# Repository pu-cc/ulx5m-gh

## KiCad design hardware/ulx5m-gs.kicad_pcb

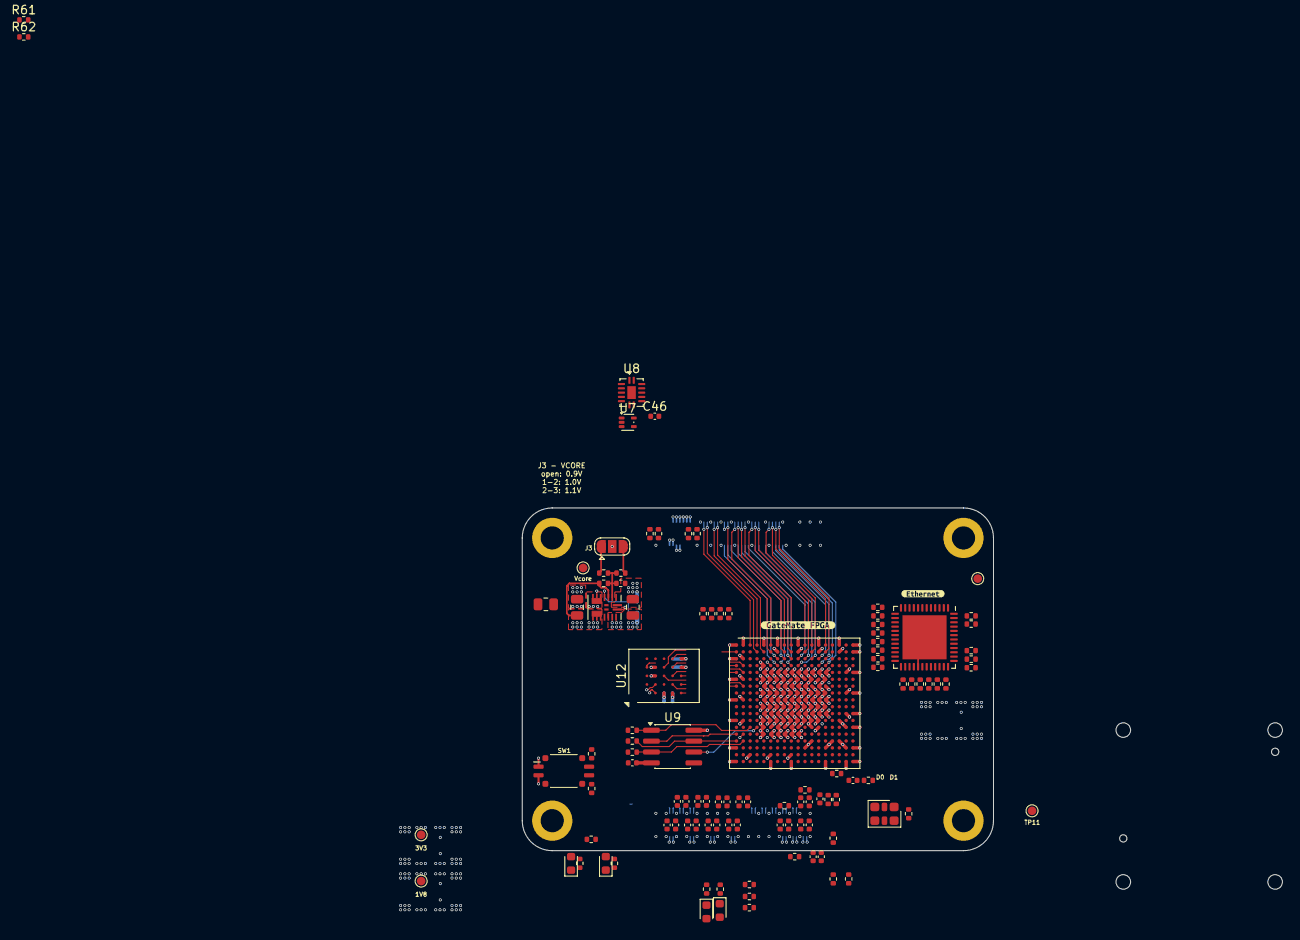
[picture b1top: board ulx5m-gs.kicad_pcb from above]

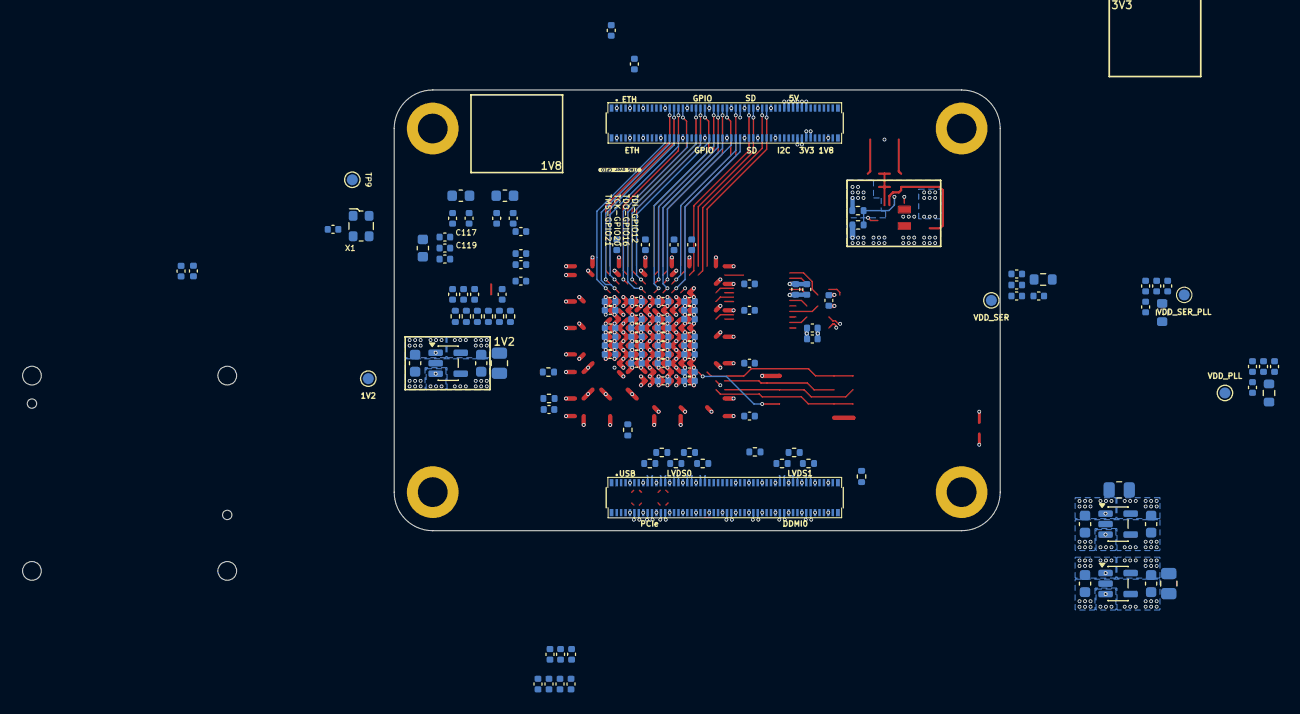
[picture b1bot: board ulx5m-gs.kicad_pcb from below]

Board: 4 copper layers, 88.7 x 44.5 mm, 243 parts (130 on the bottom side), 217 nets.

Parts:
C1, C10: 22u; C_0805_2012Metric
C2, C3, C8, C9, C11, C29: 1u; C_0603_1608Metric
C5, C6, C7, C12, C19, C20, C24, C25, C33, C59, C60, C61, C62, C63, C64, C65, C66, C87, C91, C95, C120, C121: 220n; C_0402_1005Metric
C13, C16, C21, C26, C36, C44, C51, C54, C75, C78, C86, C90, C94, C100, C122, C123, C131: 2u2; C_0402_1005Metric
C15, C18, C23, C28, C81, C82, C110, C111, C113, C119, C126, C139: 10n; C_0402_1005Metric
C31, C34, C37, C40, C42, C45, C46, C47, C48, C49, C52, C55, C56, C57, C76, C79, C80, C83, C84, C88, C89, C92, C93, C96, C97, C102, C103, C106, C107, C108, C112, C116, C117, C118, C127, C128, C129, C130, C132, C133, C134, C135, C136, C137, C138: 100n; C_0402_1005Metric
C39, C43, C50, C53, C58, C77, C98, C124, C125: 22u; C_0402_1005Metric
C104, C105, C109, C114: 10u; C_0402_1005Metric
C115: 4u7; C_0402_1005Metric
D1: green; D_0603_1608Metric
D2: red; D_0603_1608Metric
D9, D10: LED; LED_0603_1608Metric
FB1, FB2, FB3: BLM18PG121SN1D; L_0603_1608Metric
H1, H2, H3, H4: MountingHole; MountingHole_2.7mm_M2.5_DIN965_Pad
J1, J2: DF40C-100DP-0.4V_51_; HRS_DF40C-100DP-0.4V_51_
J3: Vcore_sel; SolderJumper-3_P1.3mm_Open_RoundedPad1.0x1.5mm
R1, R143: 100k; R_0402_1005Metric
R2: 51k; R_0402_1005Metric
R7, R8: 0R; R_0402_1005Metric
R9, R107, R108, R110, R112, R113: dnp; R_0402_1005Metric
R10, R11, R13, R21: 0R; R_0805_2012Metric
R12: 40k; R_0402_1005Metric
R14: 120k; R_0402_1005Metric
R15: 20k; R_0402_1005Metric
R16: 60k; R_0402_1005Metric
R23, R105, R106: 1R; R_0603_1608Metric
R24, R25, R27, R29, R30, R111, R128, R134, R138, R139, R147, R148, R149, R150: 10k; R_0402_1005Metric
R31, R32: 200R; R_0402_1005Metric
R33, R34, R35, R36, R38, R39, R66, R67, R70, R71, R72, R73, R78, R79, R84, R85, R96: 4k7; R_0402_1005Metric
R44, R45: 27; R_0402_1005Metric
R50, R51, R54, R129, R130, R131, R132, R135: 150; R_0402_1005Metric
R58: 1k5; R_0402_1005Metric
R59, R63: R300; R_0402_1005Metric
R61, R62: 5k1; R_0402_1005Metric
R89, R90, R91, R92, R93, R94, R97, R98, R99, R100, R101, R102, R104: 27R; R_0402_1005Metric
R103: 12k1; R_0402_1005Metric
R109: 200; R_0402_1005Metric
SW1: 219-2MST; SW_DIP_SPSTx02_Slide_Copal_CVS-02xB_W5.9mm_P1mm
TP1: 1V8; TestPoint_Pad_D1.0mm
TP2: 3V3; TestPoint_Pad_D1.0mm
TP3: Vcore; TestPoint_Pad_D1.0mm
TP4: 1V2; TestPoint_Pad_D1.0mm
TP6: VDD_PLL; TestPoint_Pad_D1.0mm
TP7, TP9, TP11: GND; TestPoint_Pad_D1.0mm
TP8: VDD_SER_PLL; TestPoint_Pad_D1.0mm
TP10: VDD_SER; TestPoint_Pad_D1.0mm
U1: TLV75718PDBV; SOT-23-5
U2: TLV75733PDBV; SOT-23-5
U3: MPM3833CGRH-Z
U4: GateMate-CCGM1A1; BGA-324_15.0x15.0mm_Layout18x18_P0.8mm_Ball0.45mm_Pad0.4mm_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
U5: TLV75712PDBV; SOT-23-5
U7: 74LVC1GU04DRL; SOT-553
U8: SN74AUC00; DHVQFN-14-1EP_2.5x3mm_P0.5mm_EP1x1.5mm
U9: AT25QL321-MBUE-T; SOIC-8_3.9x4.9mm_P1.27mm
U12: S27KL0641; BGA-24_6x8mm_Layout5x5_P1.0mm
U14: KSZ9031RNXCA; QFN-48-1EP_7x7mm_P0.5mm_EP5.15x5.15mm
X1: ECS-2520MV-250-xx; Oscillator_SMD_ECS_2520MV-xxx-xx-4Pin_2.5x2.0mm
X2: 511FCA100M000BAG; Oscillator_SMD_SiTime_PQFD-6L_3.2x2.5mm
kibuzzard-686AA8CB: G***; kibuzzard-686AA8CB
kibuzzard-686CE423: G***; kibuzzard-686CE423
kibuzzard-689F41CF: G***; kibuzzard-689F41CF

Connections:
+1V2: C49.1, C50.1, C51.1, C52.1, C104.1, C106.1, C108.1, C111.1, C113.1, FB2.1, FB3.1, R21.2, U4.P6 (VDD_SA), U4.P8 (VDD_SA), U4.P10 (VDD_SA), U4.U6 (VDD_SA), U4.U9 (VDD_SA), U14.14 (DVDDL), U14.18 (DVDDL), U14.23 (DVDDL), U14.26 (DVDDL), U14.30 (DVDDL), U14.39 (DVDDL)
+1V8: C43.1, C44.1, C45.1, C46.1, C47.1, C48.1, C53.1, C54.1, C55.1, C56.1, C57.1, C58.1, C75.1, C76.1, C77.1, C78.1, C79.1, C80.1, C81.1, C82.1, C83.1, C84.1, C98.1, C100.1, C102.1, C103.1, C105.1, C107.1, C110.1, C126.1, C131.1, C132.1, C139.1, J2.88, J2.90, R10.2, R30.1, R33.1, R34.1, R35.1, R36.1, R38.1, R66.1, R67.1, R70.1, R71.1, R72.1, R73.1, R96.1, R111.1, R112.1, R143.1, SW1.1, SW1.2, U4.A2 (VDD_WC), U4.A16 (VDD_EB), U4.B18 (VDD_EB), U4.C2 (VDD_WC), U4.D5 (VDD_WC), U4.E14 (VDD_EB), U4.E17 (VDD_EB), U4.F2 (VDD_WC), U4.F5 (VDD_WC), U4.F13 (VDD_EB), U4.H5 (VDD_WB), U4.J2 (VDD_WB), U4.K5 (VDD_WB), U4.M2 (VDD_WB), U4.M5 (VDD_WB), U4.N5 (VDD_WA), U4.N11 (VDD_SB), U4.N13 (VDD_SB), U4.N18 (VDD_SB), U4.P3 (VDD_WA), U4.P5 (VDD_WA), U4.R15 (VDD_SB), U4.T1 (VDD_WA), U4.T14 (VDD_CLK), U4.T18 (VDD_SB), U4.U1 (POR_EN/IO_WA_A3), U4.U3 (VDD_WA), U7.5 (VCC), U8.14 (VCC), U9.8 (VCC), U12.B4 (VCC), U12.D1 (VCCQ), U12.E4 (VCCQ), U14.16 (DVDDH), U14.34 (DVDDH), U14.40 (DVDDH), X2.6 (VDD)
+3V3: C94.1, C95.1, C96.1, C97.1, C118.1, FB1.2, J2.84, J2.86, R11.2, R58.2, R128.1, R134.1, R138.1, R139.2, U4.G14 (VDD_EA), U4.H17 (VDD_EA), U4.J14 (VDD_EA), U4.L14 (VDD_EA), U4.L17 (VDD_EA), X1.1 (Tri-State), X1.4 (VDD)
+5V: C1.1, C2.1, C3.1, C11.1, J2.77, J2.79, J2.81, J2.83, J2.85, J2.87, R1.1, U1.1 (IN), U1.3 (EN), U2.1 (IN), U2.3 (EN), U3.13 (IN), U3.14 (IN), U5.1 (IN), U5.3 (EN)
/cm4-gpio/ETH0_LEDG: J2.15, U14.17 (LED1/PHAD0/PME_N1)
/cm4-gpio/ETH0_LEDY: J2.17, U14.15 (LED2/PHYAD1)
/cm4-gpio/ETH0_N: J2.10, U14.3 (TXRXM_A)
/cm4-gpio/ETH0_P: J2.12, U14.2 (TXRXP_A)
/cm4-gpio/ETH1_N: J2.6, U14.6 (TXRXM_B)
/cm4-gpio/ETH1_P: J2.4, U14.5 (TXRXP_B)
/cm4-gpio/ETH2_N: J2.9, U14.8 (TXRXM_C)
/cm4-gpio/ETH2_P: J2.11, U14.7 (TXRXP_C)
/cm4-gpio/ETH3_N: J2.5, U14.11 (TXRXM_D)
/cm4-gpio/ETH3_P: J2.3, U14.10 (TXRXP_D)
/cm4-gpio/GPIO2: J2.58, U4.D7 (IO_NA_B5)
/cm4-gpio/GPIO3: J2.56, U4.C7 (IO_NA_A5)
/cm4-gpio/GPIO4: J2.54, U4.C8 (IO_NA_A6)
/cm4-gpio/GPIO5: J2.34, U4.C12 (IO_NB_B5)
/cm4-gpio/GPIO6: J2.30, U4.C13 (IO_NB_B6)
/cm4-gpio/GPIO7: J2.37, U4.B11 (IO_NB_A2)
/cm4-gpio/GPIO8: J2.39, U4.A11 (IO_NB_B2)
/cm4-gpio/GPIO9: J2.40, U4.C11 (IO_NB_B3)
/cm4-gpio/GPIO10: J2.44, U4.C10 (IO_NB_B1)
/cm4-gpio/GPIO11: J2.38, U4.D10 (IO_NB_A1)
/cm4-gpio/GPIO12: J2.31, R147.1, U4.A12 (IO_NB_B4)
/cm4-gpio/GPIO13: J2.28, U4.C14 (IO_NB_B8)
/cm4-gpio/GPIO14: J2.55, U4.B6 (IO_NA_B4)
/cm4-gpio/GPIO15: J2.51, U4.A6 (IO_NA_A4)
/cm4-gpio/GPIO16: J2.29, R148.1, U4.B12 (IO_NB_A4)
/cm4-gpio/GPIO17: J2.50, U4.D8 (IO_NA_B6)
/cm4-gpio/GPIO18: J2.49, U4.B8 (IO_NA_B7)
/cm4-gpio/GPIO19: J2.26, U4.D13 (IO_NB_A6)
/cm4-gpio/GPIO20: J2.27, R149.1, U4.A14 (IO_NB_B7)
/cm4-gpio/GPIO21: J2.25, R150.1, U4.B14 (IO_NB_A7)
/cm4-gpio/GPIO22: J2.46, U4.D9 (IO_NA_B8)
/cm4-gpio/GPIO23: J2.47, U4.A8 (IO_NA_A7)
/cm4-gpio/GPIO24: J2.45, U4.B9 (IO_NB_A0)
/cm4-gpio/GPIO25: J2.41, U4.A9 (IO_NB_B0)
/cm4-gpio/GPIO26: J2.24, U4.D14 (IO_NB_A8)
/cm4-gpio/GPIO27: J2.48, U4.C9 (IO_NA_A8)
/cm4-gpio/SCL0: J2.80, U4.C5 (IO_NA_B2)
/cm4-gpio/SDA0: J2.82, U4.B3 (IO_NA_B0)
/cm4-gpio/SD_CLK: J2.57, U4.C6 (IO_NA_A3)
/cm4-gpio/SD_CMD: J2.62, U4.D6 (IO_NA_B3)
/cm4-gpio/SD_DAT0: J2.63, U4.A4 (IO_NA_A1)
/cm4-gpio/SD_DAT1: J2.67, U4.B4 (IO_NA_B1)
/cm4-gpio/SD_DAT2: J2.69, U4.A3 (IO_NA_A0)
/cm4-gpio/SD_DAT3: J2.61, U4.B5 (IO_NA_A2)
/cm4-gpio/nLED_act: J2.21, U7.4, U8.9
/cm4-hsio/DDMI0_CLK_N: C66.2, J1.90
/cm4-hsio/DDMI0_CLK_P: C65.2, J1.88
/cm4-hsio/DDMI0_TX0_N: C60.2, J1.84
/cm4-hsio/DDMI0_TX0_P: C59.2, J1.82
/cm4-hsio/DDMI0_TX1_N: C62.2, J1.78
/cm4-hsio/DDMI0_TX1_P: C61.2, J1.76
/cm4-hsio/DDMI0_TX2_N: C64.2, J1.72
/cm4-hsio/DDMI0_TX2_P: C63.2, J1.70
/cm4-hsio/DDMI1_CLK_N: C25.2, J1.66
/cm4-hsio/DDMI1_CLK_P: C24.2, J1.64
/cm4-hsio/DDMI1_TX0_N: C6.2, J1.60
/cm4-hsio/DDMI1_TX0_P: C5.2, J1.58
/cm4-hsio/DDMI1_TX1_N: C12.2, J1.54
/cm4-hsio/DDMI1_TX1_P: C7.2, J1.52
/cm4-hsio/DDMI1_TX2_N: C20.2, J1.48
/cm4-hsio/DDMI1_TX2_P: C19.2, J1.46
/cm4-hsio/LVDS0_C_N: J1.27, R50.2, U4.T9 (IO_SA_B6)
/cm4-hsio/LVDS0_C_P: J1.29, R50.1, U4.R9 (IO_SA_A6)
/cm4-hsio/LVDS0_D0_N: J1.15, R51.2, U4.V10 (IO_SA_B8)
/cm4-hsio/LVDS0_D0_P: J1.17, R51.1, U4.U10 (IO_SA_A8)
/cm4-hsio/LVDS0_D1_N: J1.21, R54.2, U4.T10 (IO_SA_B7)
/cm4-hsio/LVDS0_D1_P: J1.23, R54.1, U4.R10 (IO_SA_A7)
/cm4-hsio/LVDS0_D2_N: J1.33, R130.2, U4.V8 (IO_SA_B5)
/cm4-hsio/LVDS0_D2_P: J1.35, R130.1, U4.U8 (IO_SA_A5)
/cm4-hsio/LVDS0_D3_N: J1.39, R131.2, U4.T8 (IO_SA_B4)
/cm4-hsio/LVDS0_D3_P: J1.41, R131.1, U4.R8 (IO_SA_A4)
/cm4-hsio/LVDS1_C_N: J1.87, R129.2, U4.T6 (IO_SA_B1)
/cm4-hsio/LVDS1_C_P: J1.89, R129.1, U4.R6 (IO_SA_A1)
/cm4-hsio/LVDS1_D0_N: J1.75, R132.2, U4.V7 (IO_SA_B3)
/cm4-hsio/LVDS1_D0_P: J1.77, R132.1, U4.U7 (IO_SA_A3)
/cm4-hsio/LVDS1_D1_N: J1.81, R135.2, U4.T7 (IO_SA_B2)
/cm4-hsio/LVDS1_D1_P: J1.83, R135.1, U4.R7 (IO_SA_A2)
/cm4-hsio/PCIe_CLK_N: C137.2, J1.12
/cm4-hsio/PCIe_CLK_P: C136.2, J1.10
/cm4-hsio/PCIe_RX_N: J1.18, R107.2, U4.V11 (SER_RX_N)
/cm4-hsio/PCIe_RX_P: J1.16, R107.1, U4.U11 (SER_RX_P)
/cm4-hsio/PCIe_TX_N: C135.2, J1.24
/cm4-hsio/PCIe_TX_P: C134.2, J1.22
/cm4-hsio/USB_N: J1.3, R44.2
/cm4-hsio/USB_OTG_ID: J1.1, U4.K16 (IO_EA_A3)
/cm4-hsio/USB_P: J1.5, R45.2, R58.1
/config/CFG_DONE: U4.V3 (IO_WA_B2/CFG_DONE), U7.2
/config/JTAG_CFG_MD0: R29.1, U4.R5 (CFG_MD0/IO_WA_A0)
/config/JTAG_CFG_MD1: R27.1, U4.T5 (CFG_MD1/IO_WA_B0)
/config/JTAG_CFG_MD2: R25.1, SW1.4, U4.U4 (CFG_MD2/IO_WA_A1)
/config/JTAG_CFG_MD3: R24.1, SW1.3, U4.V4 (CFG_MD3/IO_WA_B1)
/config/JTAG_TCK: R39.1, R149.2, U4.R3 (JTAG_TCK/IO_WA_A5)
/config/JTAG_TDI: R36.2, R147.2, U4.T2 (JTAG_TDI/IO_WA_A4)
/config/JTAG_TDO: R148.2, U4.U2 (JTAG_TDO/IO_WA_B3)
/config/JTAG_TMS: R34.2, R150.2, U4.T3 (JTAG_TMS/IO_WA_B4)
/config/SPI_CSN: R38.2, U4.N3 (IO_WA_A8/~SPI_CS), U9.1 (~CS)
/config/SPI_IO0: U4.P2 (IO_WA_B7/SPI_D0), U9.5 (SI/SIO0)
/config/SPI_IO1: U4.P1 (IO_WA_A7/SPI_D1), U9.2 (SO/SIO1)
/config/SPI_IO2: R35.2, U4.R2 (IO_WA_B6/SPI_D2), U9.3 (~WP/SIO2)
/config/SPI_IO3: R33.2, U4.R1 (IO_WA_A6/SPI_D3), U9.7 (~RESET/SIO3)
/config/SPI_SCK: U4.N4 (IO_WA_B8/SPI_CLK), U9.6 (SCLK)
/config/~CFG_FAIL: U4.V2 (IO_WA_A2/~CFG_FAILED), U8.1
/ethernet/ETH_CLK: R104.2, U4.E16 (IO_EB_A3), U14.46 (XI)
/ethernet/PHY_CLK: R104.1, X1.3 (OUT)
/ethernet/RGMII_INT_N: R67.2, U4.C15 (IO_EB_B7), U14.38 (INT_N/PME_N2)
/ethernet/RGMII_MDC: U4.C16 (IO_EB_B6), U14.36 (MDC)
/ethernet/RGMII_MDIO: R96.2, U4.D16 (IO_EB_A6), U14.37 (MDIO)
/ethernet/RGMII_REFCLK: R66.2, U4.A15 (IO_EB_B8), U14.41 (CLK125_NDO/LED_MODE)
/ethernet/RGMII_RST_N: U4.E15 (IO_EB_B3), U14.42 (RESET_N)
/ethernet/RGMII_RX0: R98.1, U14.32 (RXD0/MODE0)
/ethernet/RGMII_RX1: R99.1, U14.31 (RXD1/MODE1)
/ethernet/RGMII_RX2: R100.1, U14.28 (RXD2/MODE2)
/ethernet/RGMII_RX3: R101.1, U14.27 (RXD3/MODE3)
/ethernet/RGMII_RXD0: R70.2, R98.2, U4.F18 (IO_EB_A0)
/ethernet/RGMII_RXD1: R71.2, R99.2, U4.F17 (IO_EB_B0)
/ethernet/RGMII_RXD2: R72.2, R100.2, U4.F16 (IO_EB_A1)
/ethernet/RGMII_RXD3: R73.2, R101.2, U4.F15 (IO_EB_B1)
/ethernet/RGMII_RX_CK: R102.1, U14.35 (RX_CLK/PHYAD2)
/ethernet/RGMII_RX_CLK: R78.1, R102.2, U4.D15 (IO_EB_A7)
/ethernet/RGMII_RX_D: R97.1, U14.33 (RX_DV/CLK125_EN)
/ethernet/RGMII_RX_DV: R79.1, R97.2, U4.B15 (IO_EB_A8)
/ethernet/RGMII_TX0: R89.2, U4.A17 (IO_EB_B5)
/ethernet/RGMII_TX1: R90.2, U4.B17 (IO_EB_A5)
/ethernet/RGMII_TX2: R91.2, U4.C17 (IO_EB_B4)
/ethernet/RGMII_TX3: R92.2, U4.C18 (IO_EB_A4)
/ethernet/RGMII_TXD0: R89.1, U14.19 (TXD0)
/ethernet/RGMII_TXD1: R90.1, U14.20 (TXD1)
/ethernet/RGMII_TXD2: R91.1, U14.21 (TXD2)
/ethernet/RGMII_TXD3: R92.1, U14.22 (TXD3)
/ethernet/RGMII_TXE: R93.2, U4.D18 (IO_EB_A2)
/ethernet/RGMII_TXEN: R93.1, U14.25 (TX_EN)
/ethernet/RGMII_TX_CK: R94.2, U4.D17 (IO_EB_B2)
/ethernet/RGMII_TX_CLK: R94.1, U14.24 (GTX_CLK)
/lvds/ALED0: D9.1 (K), R59.1
/lvds/ALED1: D10.1 (K), R63.1
/lvds/DDMI0_HS_CLK_N: C66.1, U4.P13 (IO_SB_B7)
/lvds/DDMI0_HS_CLK_P: C65.1, U4.P12 (CLK1/IO_SB_A7)
/lvds/DDMI0_HS_TX0_N: C60.1, U4.R11 (IO_SB_B4)
/lvds/DDMI0_HS_TX0_P: C59.1, U4.P11 (IO_SB_A4)
/lvds/DDMI0_HS_TX1_N: C62.1, U4.R14 (IO_SB_B5)
/lvds/DDMI0_HS_TX1_P: C61.1, U4.R13 (CLK3/IO_SB_A5)
/lvds/DDMI0_HS_TX2_N: C64.1, U4.P15 (IO_SB_B6)
/lvds/DDMI0_HS_TX2_P: C63.1, U4.P14 (CLK2/IO_SB_A6)
/lvds/DDMI1_HS_CLK_N: C25.1, U4.M18 (IO_SB_B3)
/lvds/DDMI1_HS_CLK_P: C24.1, U4.M17 (IO_SB_A3)
/lvds/DDMI1_HS_TX0_N: C6.1, U4.U18 (IO_SB_B0)
/lvds/DDMI1_HS_TX0_P: C5.1, U4.U17 (IO_SB_A0)
/lvds/DDMI1_HS_TX1_N: C12.1, U4.R18 (IO_SB_B1)
/lvds/DDMI1_HS_TX1_P: C7.1, U4.R17 (IO_SB_A1)
/lvds/DDMI1_HS_TX2_N: C20.1, U4.P18 (IO_SB_B2)
/lvds/DDMI1_HS_TX2_P: C19.1, U4.P17 (IO_SB_A2)
/lvds/LED0: D9.2 (A), U4.U5 (IO_SA_A0)
/lvds/LED1: D10.2 (A), U4.V5 (IO_SA_B0)
/memory/HR_CK_N: U4.E4 (IO_WC_B4), U12.B1 (~CK)
/memory/HR_CK_P: U4.E3 (IO_WC_A4), U12.B2 (CK)
/memory/HR_DQ0: U4.E2 (IO_WC_B3), U12.D3 (DQ0)
/memory/HR_DQ1: U4.G2 (IO_WC_B0), U12.D2 (DQ1)
/memory/HR_DQ2: U4.G3 (IO_WC_A1), U12.C4 (DQ2)
/memory/HR_DQ3: U4.G4 (IO_WC_B1), U12.D4 (DQ3)
/memory/HR_DQ4: U4.F3 (IO_WC_A2), U12.D5 (DQ4)
/memory/HR_DQ5: U4.F4 (IO_WC_B2), U12.E3 (DQ5)
/memory/HR_DQ6: U4.E1 (IO_WC_A3), U12.E2 (DQ6)
/memory/HR_DQ7: U4.G1 (IO_WC_A0), U12.E1 (DQ7)
/memory/HR_RWDS: U4.D1 (IO_WC_A5), U12.C3 (RWDS)
/memory/~HR_CS: U4.D2 (IO_WC_B5), U12.A3 (~CS)
/memory/~HR_RST: U4.B1 (IO_WC_A8), U12.A4 (~RESET)
/power/DC_1V2: C29.1, R21.1, TP4.1, U5.5 (OUT)
/power/DC_1V8: C8.1, R10.1, TP1.1, U1.5 (OUT)
/power/DC_3V3: C9.1, R11.1, TP2.1, U2.5 (OUT)
/power/DC_OUT: C10.1, R13.1, R15.1, TP3.1, U3.3 (OUT_S), U3.8 (OUT), U3.9 (OUT), U3.10 (OUT)
/power/SW: U3.5 (SW), U3.6 (SW), U3.7 (SW), U3.15 (SW)
/power/TESTMODE: R7.1, U4.U16 (GND)
/serdes/PCIe_TX_BC_N: C135.1, R110.2, U4.V13 (SER_TX_N)
/serdes/PCIe_TX_BC_P: C134.1, R110.1, U4.U13 (SER_TX_P)
/serdes/SER_CK_N: C130.2, R108.2, U4.T13 (SER_CLK_N)
/serdes/SER_CK_P: C129.2, R108.1, U4.T12 (SER_CLK)
/serdes/SER_CLK_N: C130.1, C137.1, X2.5 (OUT-)
/serdes/SER_CLK_P: C129.1, C136.1, X2.4 (OUT+)
/serdes/SER_PORT_ADJ: C133.1, R112.2, R113.1, U4.V15 (POR_ADJ)
GND: C1.2, C2.2, C3.2, C8.2, C9.2, C10.2, C11.2, C13.2, C15.2, C16.2, C18.2, C21.2, C23.2, C26.2, C28.2, C29.2, C31.2, C33.2, C34.2, C36.2, C37.2, C39.2, C40.2, C42.2, C43.2, C44.2, C45.2, C46.2, C47.2, C48.2, C49.2, C50.2, C51.2, C52.2, C53.2, C54.2, C55.2, C56.2, C57.2, C58.2, C75.2, C76.2, C77.2, C78.2, C79.2, C80.2, C81.2, C82.2, C83.2, C84.2, C86.2, C87.2, C88.2, C89.2, C90.2, C91.2, C92.2, C93.2, C94.2, C95.2, C96.2, C97.2, C98.2, C100.2, C102.2, C103.2, C104.2, C105.2, C106.2, C107.2, C108.2, C109.2, C110.2, C111.2, C112.2, C113.2, C114.2, C115.2, C116.2, C117.2, C118.2, C119.2, C120.2, C121.2, C122.2, C123.2, C124.2, C125.2, C126.2, C127.2, C128.2, C131.2, C132.2, C133.2, C138.2, C139.2, D1.1 (K), D2.1 (K), H1.1, H2.1, H3.1, H4.1, J1.7, J1.8, J1.13, J1.14, J1.19, J1.20, J1.25, J1.26, J1.31, J1.32, J1.37, J1.38, J1.44, J1.50, J1.55, J1.56, J1.61, J1.62, J1.67, J1.68, J1.73, J1.74, J1.79, J1.80, J1.85, J1.86, J1.91, J1.92, J1.97, J1.98, J2.1, J2.2, J2.7, J2.8, J2.13, J2.14, J2.22, J2.23, J2.32, J2.33, J2.42, J2.43, J2.52, J2.53, J2.59, J2.60, J2.65, J2.66, J2.71, J2.74, J2.98, J3.2, R2.2, R7.2, R8.2, R12.1, R24.2, R25.2, R27.2, R29.2, R30.2, R39.2, R59.2, R61.1, R62.1, R63.2, R78.2, R79.2, R84.2, R85.2, R103.1, R109.1, R113.2, TP7.1, TP9.1, TP11.1, U1.2 (GND), U1.4 (NC), U2.2 (GND), U2.4 (NC), U3.1 (AGND), U3.16 (PGND), U4.A1 (GND), U4.A7 (GND), U4.A10 (GND), U4.A13 (GND), U4.A18 (GND), U4.B16 (GND), U4.C1 (GND), U4.E5 (GND), U4.E7 (GND), U4.E9 (GND), U4.E11 (GND), U4.E13 (GND), U4.E18 (GND), U4.F1 (GND), U4.F6 (GND), U4.F8 (GND), U4.F10 (GND), U4.F12 (GND), U4.F14 (GND), U4.G5 (GND), U4.G7 (GND), U4.G9 (GND), U4.G11 (GND), U4.G13 (GND), U4.H6 (GND), U4.H8 (GND), U4.H10 (GND), U4.H12 (GND), U4.H14 (GND), U4.H18 (GND), U4.J1 (GND), U4.J5 (GND), U4.J7 (GND), U4.J9 (GND), U4.J11 (GND), U4.J13 (GND), U4.K6 (GND), U4.K8 (GND), U4.K10 (GND), U4.K12 (GND), U4.K14 (GND), U4.L5 (GND), U4.L7 (GND), U4.L9 (GND), U4.L11 (GND), U4.L13 (GND), U4.L18 (GND), U4.M1 (GND), U4.M6 (GND), U4.M8 (GND), U4.M10 (GND), U4.M12 (GND), U4.M16 (GND), U4.N7 (GND), U4.N9 (GND), U4.N12 (GND), U4.N17 (GND), U4.P4 (GND), U4.P7 (GND), U4.P9 (GND), U4.R12 (GND), U4.R16 (GND), U4.T4 (GND), U4.T11 (GND), U4.T17 (GND), U4.U14 (GND), U4.U15 (GND), U4.V1 (GND), U4.V6 (GND), U4.V9 (GND), U4.V14 (GND), U4.V18 (GND), U5.2 (GND), U5.4 (NC), U7.3 (GND), U8.7 (GND), U9.4 (GND), U12.B3 (VSS), U12.C1 (VSSQ), U12.E5 (VSSQ), U14.29 (VSS), U14.49 (PAD_GND), X1.2 (GND), X2.3 (GND)
GPIO_VREF: C86.1, C87.1, C88.1, C89.1, C90.1, C91.1, C92.1, C93.1, J2.78, U4.A5 (VDD_NA), U4.B7 (VDD_NA), U4.B10 (VDD_NB), U4.B13 (VDD_NB), U4.E6 (VDD_NA), U4.E8 (VDD_NA), U4.E10 (VDD_NB), U4.E12 (VDD_NB), U4.F7 (VDD_NA), U4.F11 (VDD_NB)
unnamed: C109.1, C112.1, FB1.1, U14.1 (AVDDH), U14.12 (AVDDH)
unnamed: C114.1, C116.1, FB2.2, U14.4 (AVDDL), U14.9 (AVDDL)
unnamed: D1.2 (A), R31.2
unnamed: D2.2 (A), R32.2
unnamed: J2.73, R128.2
unnamed: J2.75, R134.2
unnamed: J2.94, R61.2
unnamed: J2.96, R62.2
unnamed: J2.97, R138.2
unnamed: J2.100, R139.1
unnamed: J3.1, R14.1
unnamed: J3.3, R16.1
unnamed: R8.1, U4.V16 (GND)
unnamed: R31.1, U8.8, U8.12
unnamed: R32.1, U8.3, U8.4
unnamed: R1.2, R2.1, U3.4 (EN)
unnamed: R12.2, R14.2, R15.2, R16.2, U3.2 (FB)
unnamed: R109.2, U4.V12 (SER_RTERM)
unnamed: R45.1, U4.M15 (IO_EA_A0)
unnamed: R44.1, U4.M14 (IO_EA_B0)
unnamed: R9.1, U4.N16 (NC)
unnamed: U8.2, U8.6
unnamed: U8.10, U8.11
unnamed: C115.1, C117.1, C119.1, FB3.2, U14.44 (AVDDL_PLL)
unnamed: R103.2, U14.48 (ISET)
unnamed: R143.2, X2.1 (OE)
PWR_BTN: J2.92, U4.B2 (IO_WC_B8)
RST_N: C138.1, J2.72, J2.99, R111.2, U4.T15 (RST_N), U8.5, U8.13
VDD_CORE: C13.1, C15.1, C16.1, C18.1, C21.1, C23.1, C26.1, C28.1, C31.1, C33.1, C34.1, C36.1, C37.1, C39.1, C40.1, C120.1, C121.1, C122.1, C123.1, C124.1, C125.1, R13.2, R23.1, R105.1, R106.1, U4.F9 (VDD), U4.G6 (VDD), U4.G8 (VDD), U4.G10 (VDD), U4.G12 (VDD), U4.H7 (VDD), U4.H9 (VDD), U4.H11 (VDD), U4.H13 (VDD), U4.J6 (VDD), U4.J8 (VDD), U4.J10 (VDD), U4.J12 (VDD), U4.K7 (VDD), U4.K9 (VDD), U4.K11 (VDD), U4.K13 (VDD), U4.L6 (VDD), U4.L8 (VDD), U4.L10 (VDD), U4.L12 (VDD), U4.M7 (VDD), U4.M9 (VDD), U4.M11 (VDD), U4.M13 (VDD), U4.N6 (VDD), U4.N8 (VDD), U4.N10 (VDD)
VDD_PLL: C42.1, R23.2, TP6.1, U4.P16 (VDD_PLL)
VDD_SER: C128.1, R9.2, R106.2, TP10.1, U4.U12 (VDD_SER), U4.V17 (VDD_SER)
VDD_SER_PLL: C127.1, R105.2, TP8.1, U4.T16 (VDD_SER_PLL)

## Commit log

2025-11-26 fix #26 fix #24
2025-11-26 Initial v4 for production
2026-01-27 power: change gpio dc converter to ldo
2026-01-27 pcb: remove socket user drawings
2026-01-27 power: removed rc filters from gpio domains
2026-01-27 lvds: remove unused wires and components
2026-01-27 ethernet: remove push buttons
2026-01-28 lvds: move leds, add ddmi1
2026-01-28 config: remove jtag header
2026-02-23 ram: rename to memory, switch to hyperram
2026-02-23 serdes: use +1V8 instead of `VDD_CLK`
2026-02-23 power: reduce decoupling capacitors
2026-02-23 minor schematic revisions
2026-02-23 ethernet: simplify usb interface
2026-02-23 big oopsie: change to 4 layer pcb, needs full revision

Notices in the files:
parts and their libraries:
project_license: CERN-OHL-S v2
